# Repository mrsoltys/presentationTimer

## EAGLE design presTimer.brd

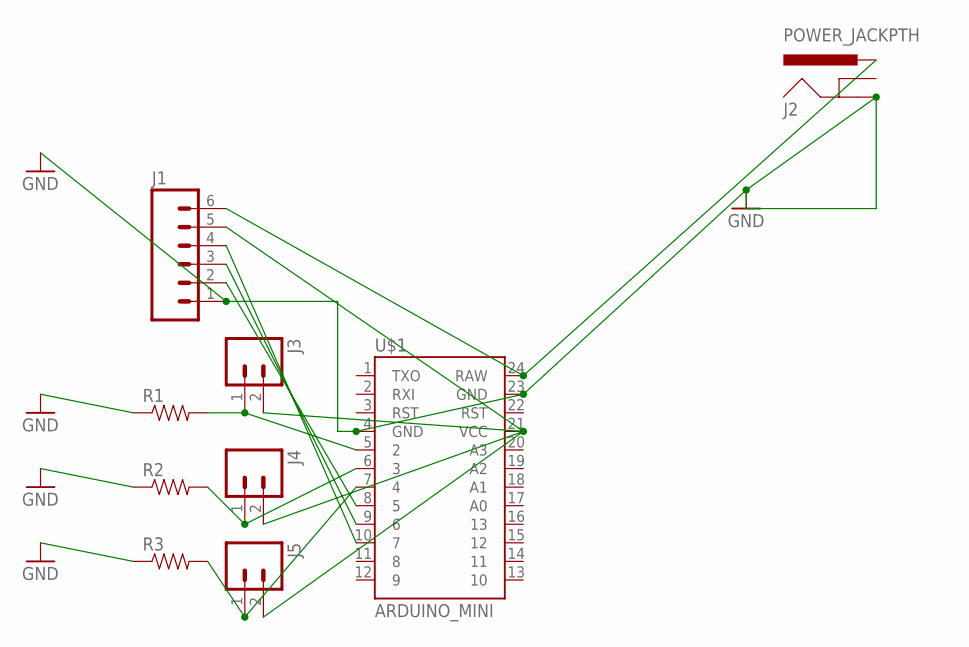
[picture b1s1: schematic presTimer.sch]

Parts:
J1: M06POLAR; MOLEX-1X6
J2: POWER_JACKPTH; POWER_JACK_PTH
J3, J4, J5: M02LOCK; 1X02_LOCK
R1, R2, R3: RESISTORAXIAL-0.3; AXIAL-0.3
U$1: ARDUINO_MINI

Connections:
GND: J1.1, J2.GND, R1.P$1 (1), R2.P$1 (1), R3.P$1 (1), U$1.4 (GND), U$1.23 (GND)
unnamed: J1.2, U$1.8 (5)
unnamed: J5.1, R3.P$2 (2), U$1.7 (4)
unnamed: J4.1, R2.P$2 (2), U$1.6 (3)
unnamed: J3.1, R1.P$2 (2), U$1.5 (2)
unnamed: J1.6, J2.PWR, U$1.24 (RAW)
unnamed: J1.5, J3.2, J4.2, J5.2, U$1.21 (VCC)
unnamed: J1.3, U$1.9 (6)
unnamed: J1.4, U$1.10 (7)

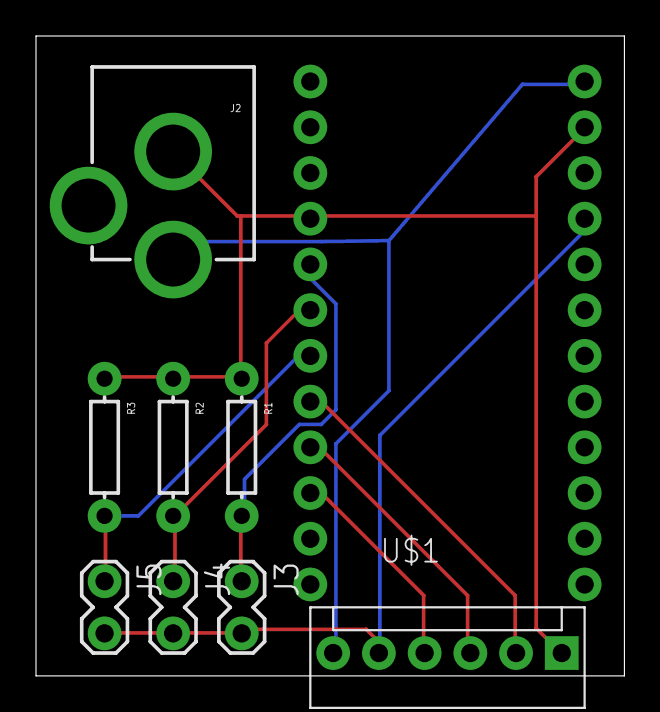
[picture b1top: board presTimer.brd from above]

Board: 2 copper layers, 32.7 x 35.5 mm, 9 parts (0 on the bottom side), 9 nets.

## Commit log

2017-03-03 Uploaded generic box for laser cutting
2017-03-06 Updated code for 4 digits
2017-03-09 Added eagle files
2017-03-16 Updated circuit board layout
2017-03-16 fixed modulo error
2017-03-16 Added stop / Clear functionality
2017-03-16 fixed comments
2017-03-16 deleted system files
2017-03-16 Added variable to correct for error.
    timer was const. 0.1% fast, so I fixed that.
2017-03-17 Updated Comments
2018-10-10 Temp Fixes
    Temp fixes because last digit is burnt out. Note, changed line 133 from 2 to 3, and multipled number by 10 on line 118.
2023-02-17 Back to working with 4 digits

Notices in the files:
parts and their libraries:
SparkFun-Connectors: Licensing: Creative Commons ShareAlike 4.0 International - https://creativecommons.org/licenses/by-sa/4.0
